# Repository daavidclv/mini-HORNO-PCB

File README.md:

# 🔥 Mini Horno — Diseño de PCB en KiCad

Diseño completo de PCB para un mini horno, desde el esquemático hasta los ficheros de fabricación (Gerbers).

## 📋 Descripción

Proyecto de diseño electrónico centrado en la placa de control de un mini horno: esquemático, layout, y generación de todos los archivos necesarios para su fabricación (Gerbers y taladros). Incluye la PCB ya fabricada y montada.

## 🛠️ Stack técnico

- **Diseño de PCB:** KiCad (esquemático + layout)
- **Fabricación:** Gerbers (RS-274X) + ficheros de taladro (PTH/NPTH)

## 📁 Estructura del repositorio

- `Horno.kicad_pro` / `Horno.kicad_sch` / `Horno.kicad_pcb` — proyecto KiCad completo (esquemático + layout)
- `Horno-*.gbr` — Gerbers de cada capa (cobre, máscara, pasta, serigrafía, corte)
- `Horno-PTH.drl` / `Horno-NPTH.drl` — ficheros de taladro
- `HornoGBR.zip` — paquete de fabricación listo para enviar al fabricante de PCBs

## 📸 Resultado

## 🎯 Lo más complejo del proyecto

- Diseño del layout considerando disipación térmica y separación de pistas de potencia
- Preparación del paquete completo de fabricación (Gerbers + taladros) sin errores de DRC

## 👤 Autor

David Calvo Heredero — [LinkedIn](https://www.linkedin.com/in/david-calvo-heredero-20b20a33a) · [GitHub](https://github.com/daavidclv)

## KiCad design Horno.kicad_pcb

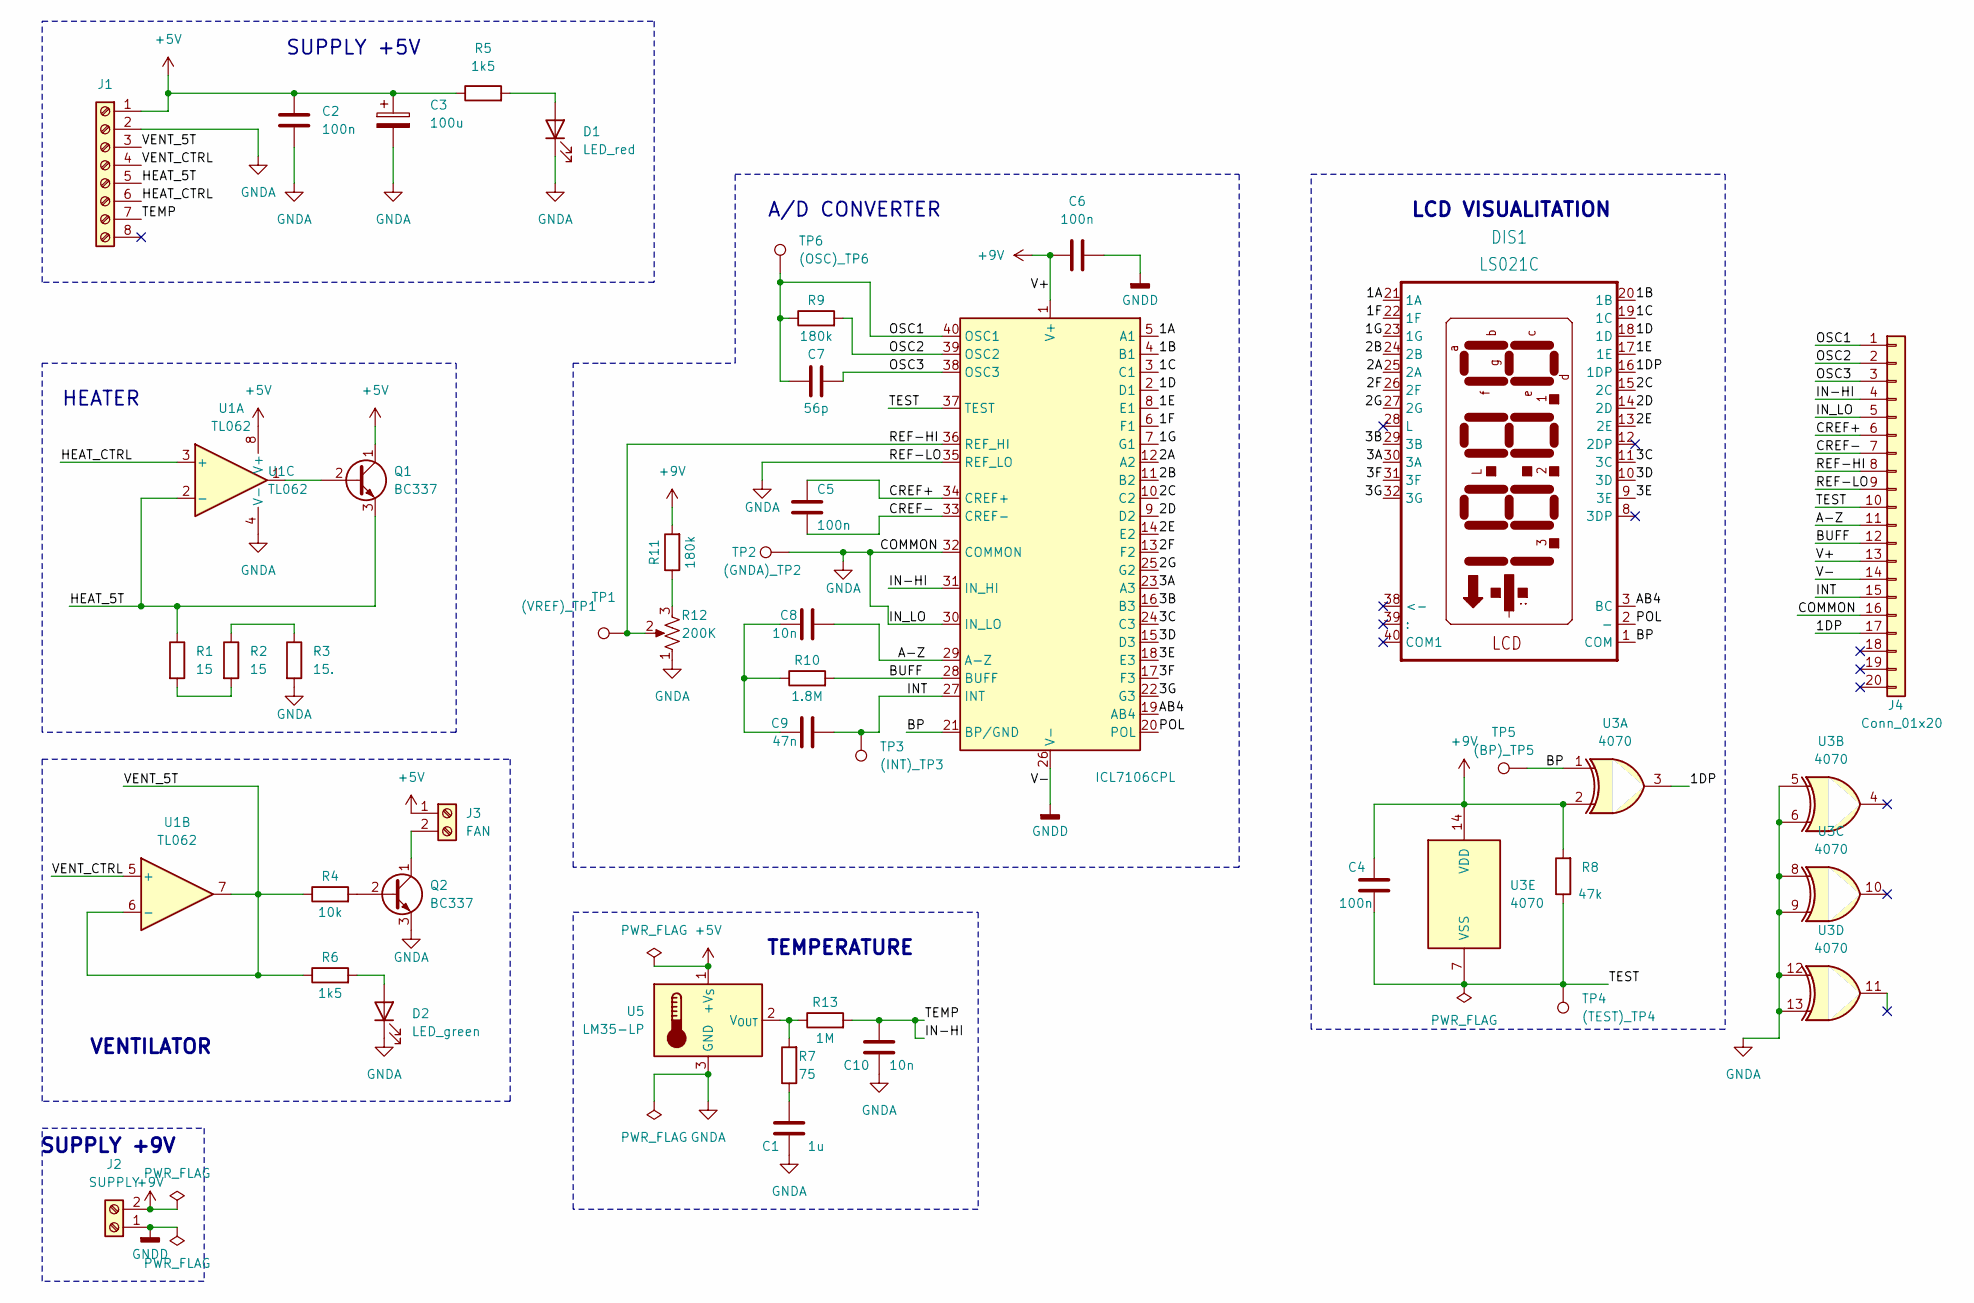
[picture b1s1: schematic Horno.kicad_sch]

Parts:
C1: 1u; C_1206_3216Metric
C2, C4, C5, C6: 100n; C_1206_3216Metric
C3: 100u; CP_Elec_5x3.9
C7: 56p; C_1206_3216Metric
C8, C10: 10n; C_1206_3216Metric
C9: 47n; C_Rect_L7.0mm_W2.5mm_P5.00mm
D1: LED_red; LED_D3.0mm
D2: LED_green; LED_D3.0mm
DIS1: LS021C; DELS021-XX-XX
J1: TerminalBlock_Phoenix_MKDS-1,5-8-5.08_1x08_P5.08mm_Horizont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
J2: SUPPLY; TerminalBlock_Phoenix_MKDS-1,5-2-5.08_1x02_P5.08mm_Horizont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
J3: FAN; TerminalBlock_Phoenix_MKDS-1,5-2-5.08_1x02_P5.08mm_Horizont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
J4: Conn_01x20; IDC-Header_2x10_P2.54mm_Vertical
Q1: BC337; TO-92L_Inline_Wide
Q2: BC337; TO-92_Inline_Wide
R1, R2: 15; R_Axial_DIN0207_L6.3mm_D2.5mm_P10.16mm_Horizontal
R3: 15.; R_Axial_DIN0207_L6.3mm_D2.5mm_P10.16mm_Horizontal
R4: 10k; R_1206_3216Metric
R5, R6: 1k5; R_1206_3216Metric
R7: 75; R_1206_3216Metric
R8: 47k; R_1206_3216Metric
R9, R11: 180k; R_1206_3216Metric
R10: 1.8M; R_1206_3216Metric
R12: 200K; Potentiometer_Bourns_3266Y_Vertical
R13: 1M; R_1206_3216Metric
TP1: (VREF)_TP1; Pin_D0.9mm_L10.0mm_W2.4mm_FlatFork
TP2: (GNDA)_TP2; Pin_D0.9mm_L10.0mm_W2.4mm_FlatFork
TP3: (INT)_TP3; Pin_D0.9mm_L10.0mm_W2.4mm_FlatFork
TP4: (TEST)_TP4; Pin_D0.9mm_L10.0mm_W2.4mm_FlatFork
TP5: (BP)_TP5; Pin_D0.9mm_L10.0mm_W2.4mm_FlatFork
TP6: (OSC)_TP6; Pin_D0.9mm_L10.0mm_W2.4mm_FlatFork
U1: TL062; DIP-8_W7.62mm_Socket
U2: ICL7106CPL; DIP-40_W15.24mm
U3: 4070
U5: LM35-LP; TO-92_Inline

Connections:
+5V: C2.1, C3.1, J1.1, J3.1, Q1.1 (C), R5.1, U1.8 (V+), U5.1 (+V_{S})
+9V: C4.1, C6.1, J2.2, J4.13, R8.2, R11.2, U2.1 (V+), U3.2, U3.14 (VDD)
/1A: DIS1.21 (1A), U2.5 (A1)
/1B: DIS1.20 (1B), U2.4 (B1)
/1C: DIS1.19 (1C), U2.3 (C1)
/1D: DIS1.18 (1D), U2.2 (D1)
/1DP: DIS1.16 (1DP), J4.17, U3.3
/1E: DIS1.17 (1E), U2.8 (E1)
/1F: DIS1.22 (1F), U2.6 (F1)
/1G: DIS1.23 (1G), U2.7 (G1)
/2A: DIS1.25 (2A), U2.12 (A2)
/2B: DIS1.24 (2B), U2.11 (B2)
/2C: DIS1.15 (2C), U2.10 (C2)
/2D: DIS1.14 (2D), U2.9 (D2)
/2E: DIS1.13 (2E), U2.14 (E2)
/2F: DIS1.26 (2F), U2.13 (F2)
/2G: DIS1.27 (2G), U2.25 (G2)
/3A: DIS1.30 (3A), U2.23 (A3)
/3B: DIS1.29 (3B), U2.16 (B3)
/3C: DIS1.11 (3C), U2.24 (C3)
/3D: DIS1.10 (3D), U2.15 (D3)
/3E: DIS1.9 (3E), U2.18 (E3)
/3F: DIS1.31 (3F), U2.17 (F3)
/3G: DIS1.32 (3G), U2.22 (G3)
/A-Z: C8.1, J4.11, U2.29 (A-Z)
/AB4: DIS1.3 (BC), U2.19 (AB4)
/BP: DIS1.1 (COM), TP5.1, U2.21 (BP/GND), U3.1
/BUFF: J4.12, R10.2, U2.28 (BUFF)
/CREF+: C5.2, J4.6, U2.34 (CREF+)
/CREF-: C5.1, J4.7, U2.33 (CREF-)
/HEAT_CTRL: J1.6, U1.3 (+)
/IN-HI: C10.1, J1.7, J4.4, R13.2, U2.31 (IN_HI)
/INT: C9.1, J4.15, TP3.1, U2.27 (INT)
/OSC1: C7.1, J4.1, R9.1, TP6.1, U2.40 (OSC1)
/OSC2: J4.2, R9.2, U2.39 (OSC2)
/OSC3: C7.2, J4.3, U2.38 (OSC3)
/POL: DIS1.2 (-), U2.20 (POL)
/REF-HI: J4.8, R12.2, TP1.1, U2.36 (REF_HI)
/TEST: C4.2, J4.10, R8.1, TP4.1, U2.37 (TEST), U3.7 (VSS)
/VENT_CTRL: J1.4, U1.5 (+)
GNDA: C1.2, C2.2, C3.2, C10.2, D1.1 (K), D2.1 (K), J1.2, J4.5, J4.9, J4.16, Q2.3 (E), R3.2, R12.1, TP2.1, U1.4 (V-), U2.30 (IN_LO), U2.32 (COMMON), U2.35 (REF_LO), U3.5, U3.6, U3.8, U3.9, U3.12, U3.13, U5.3 (GND)
GNDD: C6.2, J2.1, J4.14, U2.26 (V-)
unnamed: C1.1, R7.1
unnamed: C8.2, C9.2, R10.1
unnamed: D1.2 (A), R5.2
unnamed: D2.2 (A), R6.2
unnamed: J3.2, Q2.1 (C)
unnamed: Q1.2 (B), U1.1
unnamed: Q2.2 (B), R4.2
unnamed: R1.2, R2.2
unnamed: R2.1, R3.1
unnamed: R11.1, R12.3
unnamed: R7.2, R13.1, U5.2 (V_{OUT})

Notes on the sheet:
A/D CONVERTER
TEMPERATURE
VENTILATOR
LCD VISUALITATION
SUPPLY +9V
HEATER
SUPPLY +5V

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
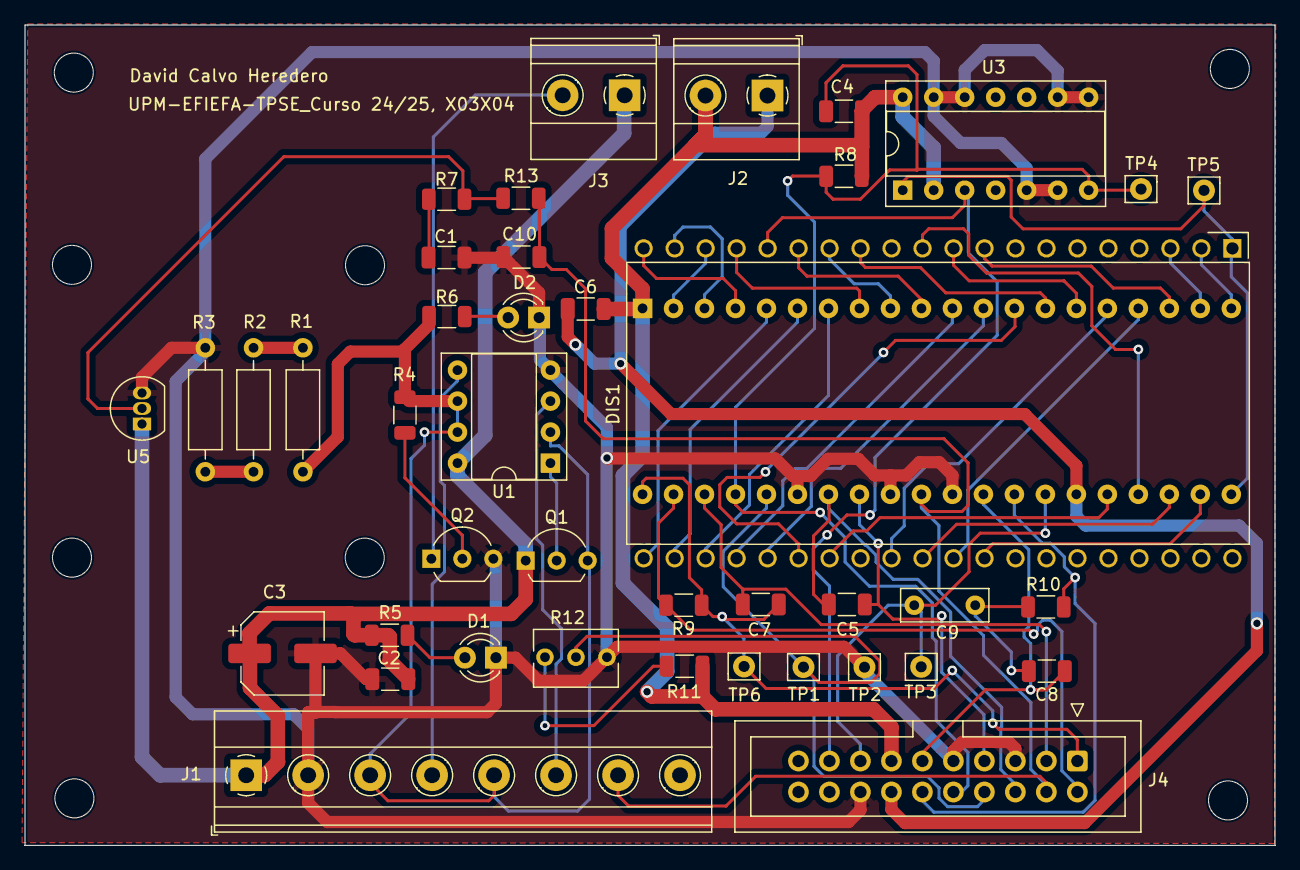
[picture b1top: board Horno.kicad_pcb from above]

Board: 2 copper layers, 102.5 x 67.2 mm, 50 parts (1 on the bottom side), 54 nets.

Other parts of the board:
PATA 1, PATA 2, PATA 3, PATA 4: MountingHole_3.2mm_M3
VENT 1, VENT 2, VENT 3, VENT 4: MountingHole_3.2mm_M3
